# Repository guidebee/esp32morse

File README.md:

# Morse Code LoRa Walkie-Talkie

A battery-powered Morse code walkie-talkie built on the **TTGO LoRa32 v1** (ESP32). Type messages in Morse code using a physical key, transmit over LoRa radio, and receive messages on an OLED display — with multi-device support, AES encryption, and configurable channels.

[Watch Demo on YouTube](https://www.youtube.com/watch?v=TG7tIteto1E)

---

## Hardware

- **Board**: TTGO LoRa32 v1 (ESP32 + SX127x LoRa + SSD1306 OLED)
- **Framework**: PlatformIO / Arduino (C++)
- **Pins**:
  - `GPIO 35` — Battery level ADC
  - `GPIO 33` — Power switch
  - `GPIO 12` — Receiver LED
  - `GPIO 13` — Bluetooth LED

---

## Features

- **Morse code input** via physical key — short press = dit (`.`), long press = dah (`-`)
- **LoRa radio** for long-range communication (up to several kilometers)
- **OLED display** split into: scrolling top screen (received messages), bottom screen (composing), top bar (uptime/title), status bar (device/signal info + battery indicator)
- **Device discovery** — auto-tracks nearby nodes by chip ID and assigns short indexes
- **AES encryption** for secure message transmission
- **Multi-channel support** — configurable channel ID and LoRa sync word
- **Buzzer feedback** — audible dit/dah tones, message sent/received sounds, error beeps
- **BLE toggle** — optional Bluetooth support
- **Battery level indicator** in the status bar corner
- **Deep sleep support** (optional, disabled by default)

---

## Controls

| Button | Action |
|--------|--------|
| **Main** (short press) | Dit (`.`) |
| **Main** (long press) | Dah (`-`) |
| **Left** | Backspace (delete last character) |
| **Right** | Insert space |
| **OK** | Send message (if composing), or enter Options menu (press 3× when idle) |

Max message length is 36 characters — long messages are auto-sent when the limit is reached.

---

## Options Menu

Press **OK** three times while idle to enter the settings menu. Navigate with Left/Right, confirm with OK.

| Option | Description |
|--------|-------------|
| Device Name | Set a display name for this node |
| Play Sound | Toggle buzzer feedback on/off |
| Bluetooth | Enable/disable BLE |
| Channel Id | Set the channel number (numeric) |
| Sync Word | Set the LoRa sync word (0x00–0xFF) |
| Input Speed | Normal (150 ms threshold) or Fast (100 ms) |
| Exit | Return to main screen |

Settings are persisted to flash via the `Preferences` library.

---

## Build & Flash

### Requirements

- [PlatformIO](https://platformio.org/) (VS Code extension or CLI)

### Libraries (auto-installed via `platformio.ini`)

- `adafruit/Adafruit BusIO`
- `thijse/ArduinoLog`
- `arduinogetstarted/ezButton`
- `sandeepmistry/LoRa`
- `adafruit/Adafruit GFX Library`
- `adafruit/Adafruit SSD1306`

### Flash

Select the environment matching your OS:

```bash
# macOS
pio run -e ttgo-lora32-v1-mac -t upload

# Windows (default COM3)
pio run -e ttgo-lora32-v1-windows -t upload

# Linux
pio run -e ttgo-lora32-v1-unix -t upload
```

Adjust the `upload_port` in `platformio.ini` if your serial port differs.

---

## Message Protocol

Each LoRa packet includes the sender's chip ID and a message type:

| Type | Description |
|------|-------------|
| `HELLO` | Broadcast on startup; announces device name and enables discovery |
| `TEXT` | A Morse-decoded text message |
| `TEXT_ACK` | Acknowledgment of a received text message |

Received messages are displayed as `<index>:<device_name> <text>` in the top screen.

---

## Photos

| | |
|---|---|
|  |  |
|  |  |

---

## License

MIT

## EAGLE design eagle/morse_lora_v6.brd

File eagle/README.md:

# ESP32 Morse LoRa - PCB Design (Eagle)

PCB design for the LoRa Morse code walkie-talkie, designed in Autodesk EAGLE 9.6.2.

## Files

| File | Description |
|------|-------------|
| `morse_lora_v6.sch` | Latest schematic |
| `morse_lora_v6.brd` | Latest board layout |
| `morse_lora_v1–v5.*` | Prior revision history |

## Board Specs

- **Size**: ~55mm × 83mm (2.2" × 3.3")
- **Layers**: 2 (Top + Bottom)
- **Components**: 29 (through-hole / PTH)
- **Software**: EAGLE 9.6.2

## Bill of Materials (v6)

| Ref | Qty | Value | Description |
|-----|-----|-------|-------------|
| ESP32LORA | 1 | — | TTGO WiFi-LoRa-32 v1 module |
| C1–C4 | 4 | 0.1µF 50V | Decoupling capacitors |
| R1–R6 | 6 | 10kΩ 1/4W | Button pull-up/pull-down resistors |
| R7–R9 | 3 | 330Ω 1/10W | LED current limiting resistors |
| D-REC | 1 | Red 5mm LED | Receive indicator |
| D-BUT | 1 | Red 5mm LED | Button press feedback |
| D-BLU | 1 | Blue 5mm LED | Radio/BT status |
| RIGHT, LEFT, OK | 3 | 6mm switch | Navigation buttons (momentary PTH) |
| MAIN | 1 | 12mm switch | Main/power button (momentary PTH) |
| SLEEP | 1 | EG1218 | Sleep mode toggle switch |
| BUZZER | 1 | — | PTH electromechanical buzzer |

## Viewing the Files

Since EAGLE `.brd`/`.sch` files are XML-based, you can view them with:

- **[Autodesk EAGLE](https://www.autodesk.com/products/eagle/)** (free tier available) — full editing
- **[KiCad](https://www.kicad.org/)** with the EAGLE import plugin — open source
- **[EasyEDA](https://easyeda.com/)** — browser-based, supports EAGLE import
- **[Gerber viewers](https://www.pcbway.com/project/OnlineGerberViewer.html)** — after exporting Gerbers from EAGLE

## Design Revision History

| Version | Notes |
|---------|-------|
| v1 | Initial design — PTH switches, 5mm LEDs, discrete passives |
| v2 | Minor iteration on v1 |
| v3 | SMD redesign (0603 resistors, 1206 LEDs, SMD buzzer) — later reverted |
| v4 | Reverted to PTH; added SLEEP switch |
| v5 | Minor iteration on v4 |
| v6 | Added 330Ω LED current-limiting resistors (R7–R9); upgraded MAIN to 12mm switch |

The v3 SMD attempt was reverted in v4, settling on a PTH-first approach for easier hand-assembly and mechanical reliability of the buttons/switches.

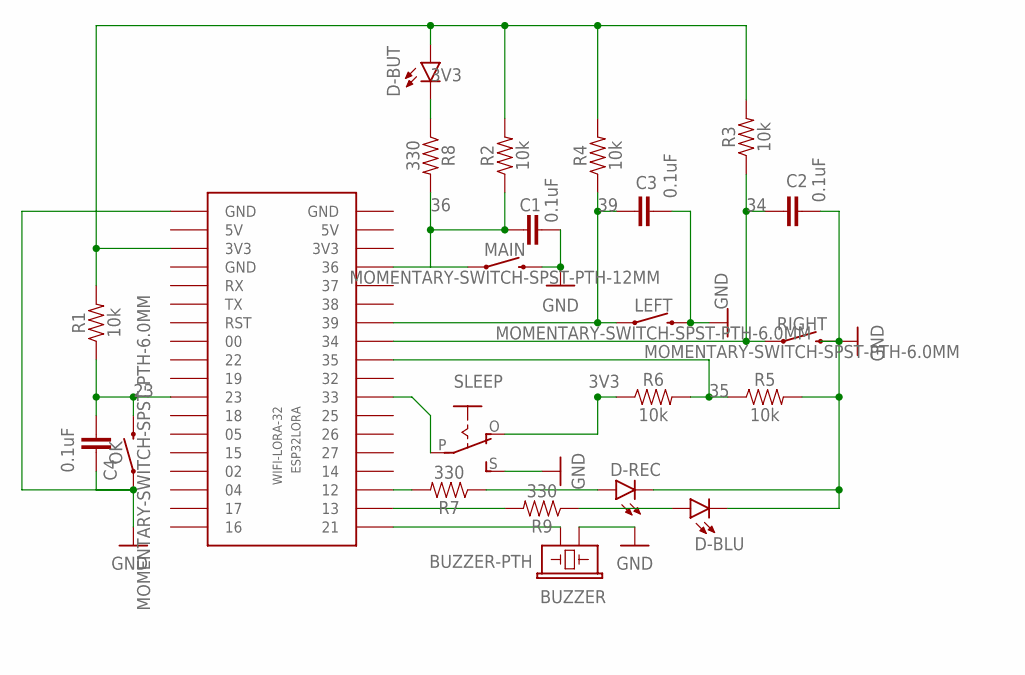
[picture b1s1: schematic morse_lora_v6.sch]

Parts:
BUZZER: BUZZER-PTH; BUZZER-12MM
C1, C2, C3, C4: 0.1uF; CAP-PTH-SMALL-KIT
D-BLU: LED5MM; LED_5MM
D-BUT: LED5MM; LED_5MM
D-REC: LED5MM; LED_5MM
ESP32LORA: WIFI-LORA-32; 2.54MM_2X18
LEFT: MOMENTARY-SWITCH-SPST-PTH-6.0MM; TACTILE_SWITCH_PTH_6.0MM
MAIN: MOMENTARY-SWITCH-SPST-PTH-12MM; TACTILE_SWITCH_PTH_12MM
OK: MOMENTARY-SWITCH-SPST-PTH-6.0MM; TACTILE_SWITCH_PTH_6.0MM
R1, R2, R3, R4, R5, R6: 10k; AXIAL-0.3-KIT
R7, R8, R9: 330; AXIAL-0.3
RIGHT: MOMENTARY-SWITCH-SPST-PTH-6.0MM; TACTILE_SWITCH_PTH_6.0MM
SLEEP: EG1218S; EG1218

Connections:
3V3: D-BUT.A, ESP32LORA.P$3 (3V3), R1.P$2 (2), R2.P$2 (2), R3.P$2 (2), R4.P$2 (2), R6.P$1 (1), SLEEP.O
23: C4.2, ESP32LORA.P$11 (23), OK.3 (2), R1.P$1 (1)
34: C2.2, ESP32LORA.P$29 (34), R3.P$1 (1), RIGHT.1
35: ESP32LORA.P$28 (35), R5.P$1 (1), R6.P$2 (2)
36: C1.2, ESP32LORA.P$33 (36), MAIN.1, R2.P$1 (1), R8.P$2 (2)
39: C3.1, ESP32LORA.P$30 (39), LEFT.1, R4.P$1 (1)
GND: BUZZER.- (2), C1.1, C2.1, C3.2, C4.1, D-BLU.K (C), D-REC.K (C), ESP32LORA.P$1 (GND), LEFT.3 (2), MAIN.3 (2), OK.1, R5.P$2 (2), RIGHT.3 (2), SLEEP.S
unnamed: ESP32LORA.P$21 (12), R7.P$2 (2)
unnamed: D-BUT.K (C), R8.P$1 (1)
unnamed: D-BLU.A, R9.P$1 (1)
unnamed: BUZZER.+ (1), ESP32LORA.P$19 (21)
unnamed: D-REC.A, R7.P$1 (1)
unnamed: ESP32LORA.P$20 (13), R9.P$2 (2)
unnamed: ESP32LORA.P$26 (33), SLEEP.P

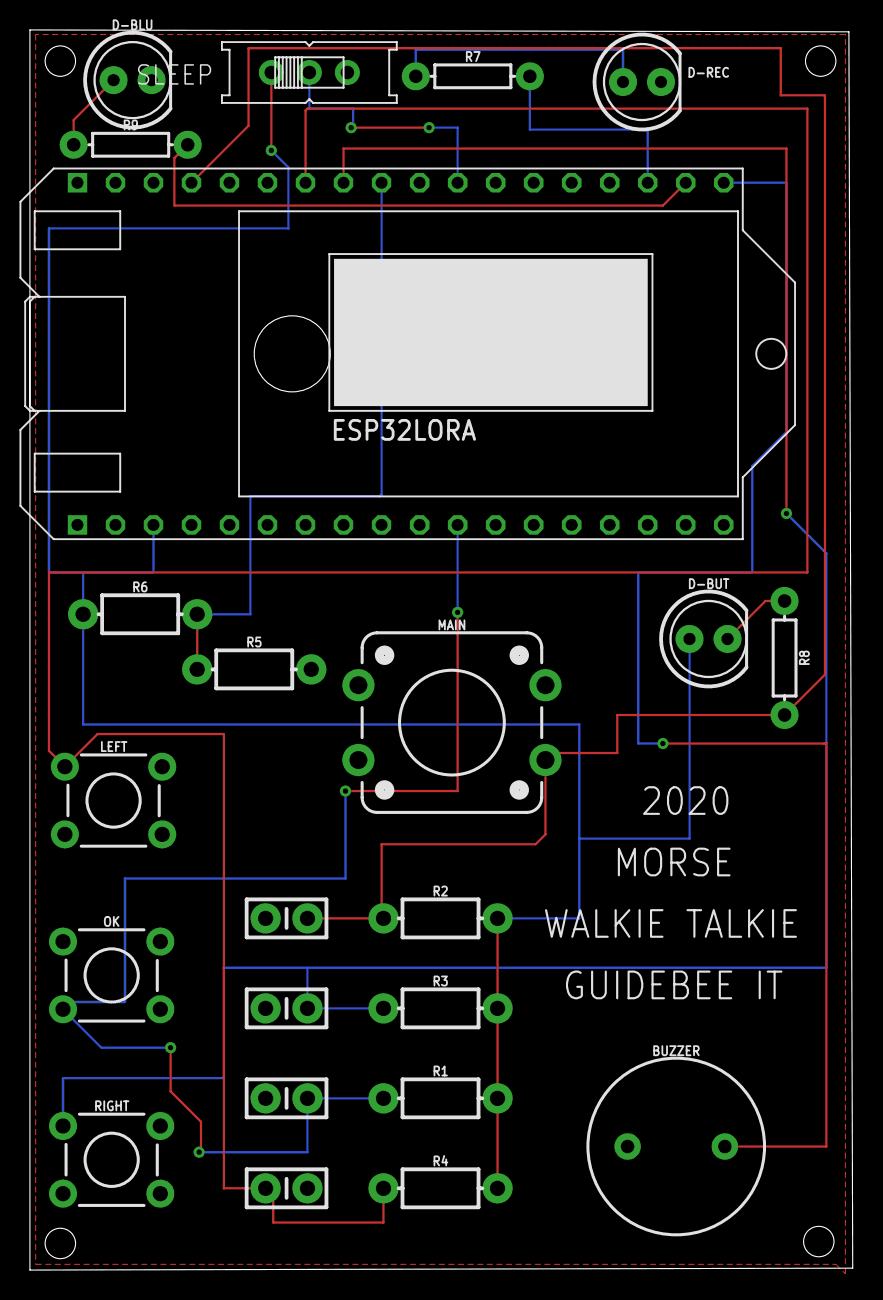
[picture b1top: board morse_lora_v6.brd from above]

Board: 2 copper layers, 55.0 x 82.9 mm, 23 parts (0 on the bottom side), 14 nets.

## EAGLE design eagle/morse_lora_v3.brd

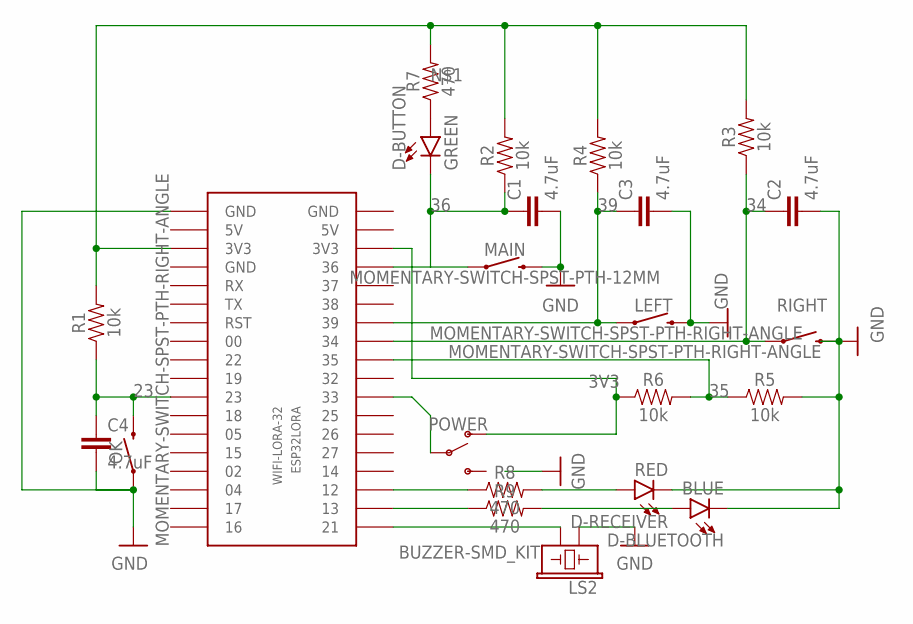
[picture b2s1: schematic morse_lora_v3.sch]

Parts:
C1, C2, C3, C4: 4.7uF; 0603
D-BLUETOOTH: BLUE; LED-1206
D-BUTTON: GREEN; LED-1206
D-RECEIVER: RED; LED-1206
ESP32LORA: WIFI-LORA-32; 2.54MM_2X18
LEFT: MOMENTARY-SWITCH-SPST-PTH-RIGHT-ANGLE; TACTILE_SWITCH_PTH_RIGHT_ANGLE
LS2: BUZZER-SMD_KIT; BUZZER-CCV-KIT
MAIN: MOMENTARY-SWITCH-SPST-PTH-12MM; TACTILE_SWITCH_PTH_12MM
OK: MOMENTARY-SWITCH-SPST-PTH-RIGHT-ANGLE; TACTILE_SWITCH_PTH_RIGHT_ANGLE
POWER: SWITCH-SPDT-SMD-RIGHT-ANGLE; SWITCH_SPST_SMD_A
R1, R2, R3, R4, R5, R6: 10k; 0603
R7, R8, R9: 470; 0603
RIGHT: MOMENTARY-SWITCH-SPST-PTH-RIGHT-ANGLE; TACTILE_SWITCH_PTH_RIGHT_ANGLE

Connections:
3V3: ESP32LORA.P$3 (3V3), ESP32LORA.P$34 (3V3), POWER.1 (O), R1.2, R2.2, R3.2, R4.2, R6.1, R7.2
23: C4.1, ESP32LORA.P$11 (23), OK.2, R1.1
34: C2.1, ESP32LORA.P$29 (34), R3.1, RIGHT.1
35: ESP32LORA.P$28 (35), R5.1, R6.2
36: C1.1, D-BUTTON.C, ESP32LORA.P$33 (36), MAIN.1, R2.1
39: C3.1, ESP32LORA.P$30 (39), LEFT.1, R4.1
GND: C1.2, C2.2, C3.2, C4.2, D-BLUETOOTH.C, D-RECEIVER.C, ESP32LORA.P$1 (GND), LEFT.2, LS2.+ (1), MAIN.3 (2), OK.1, R5.2, RIGHT.2
unnamed: D-BUTTON.A, R7.1
unnamed: D-RECEIVER.A, R8.2
unnamed: ESP32LORA.P$20 (13), R9.1
unnamed: ESP32LORA.P$19 (21), LS2.- (2)
unnamed: ESP32LORA.P$21 (12), R8.1
unnamed: D-BLUETOOTH.A, R9.2
unnamed: ESP32LORA.P$26 (33), POWER.2

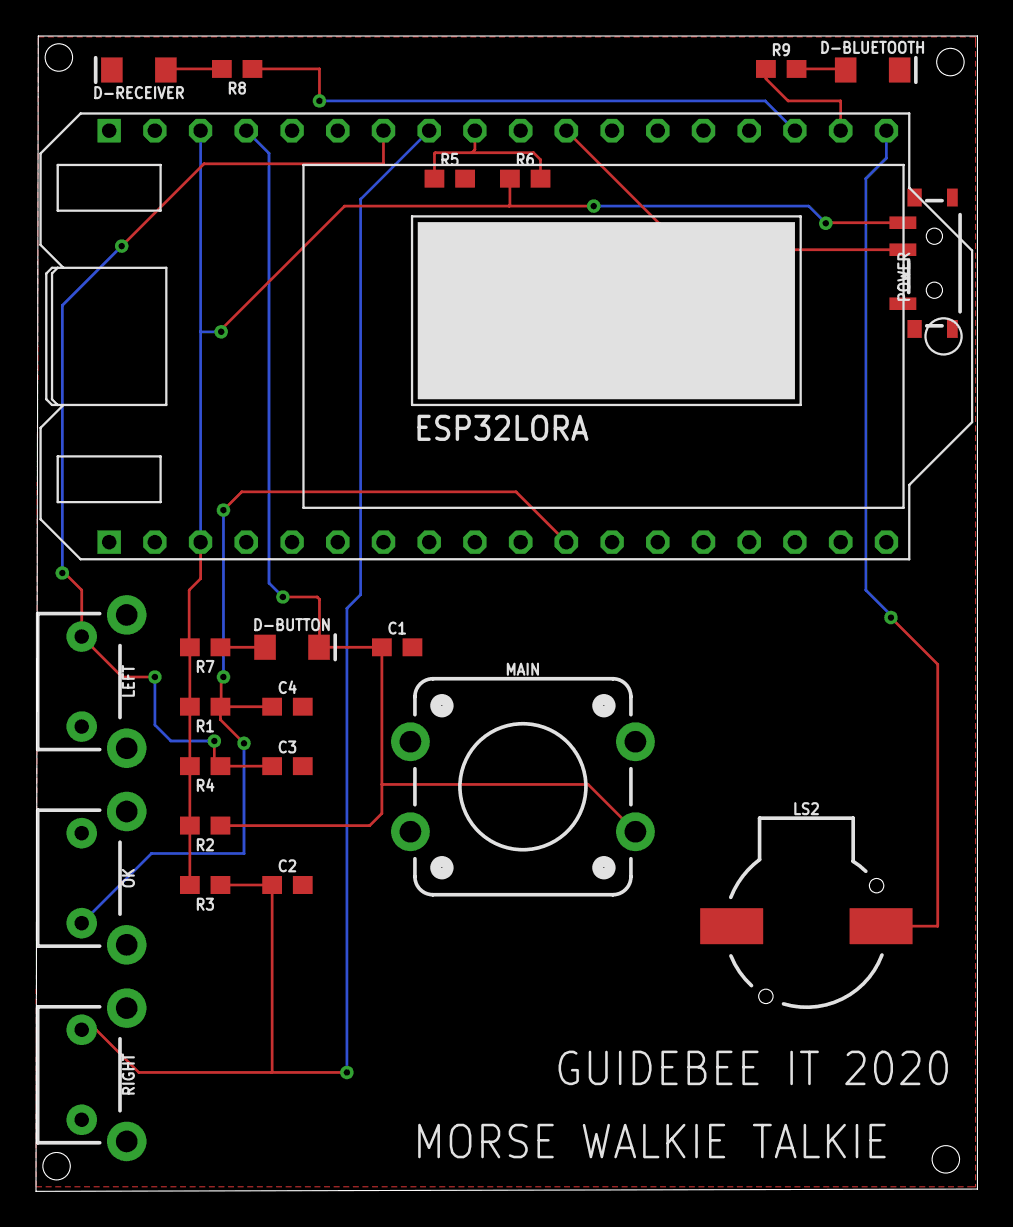
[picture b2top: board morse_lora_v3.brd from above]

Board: 2 copper layers, 52.3 x 64.2 mm, 23 parts (0 on the bottom side), 14 nets.

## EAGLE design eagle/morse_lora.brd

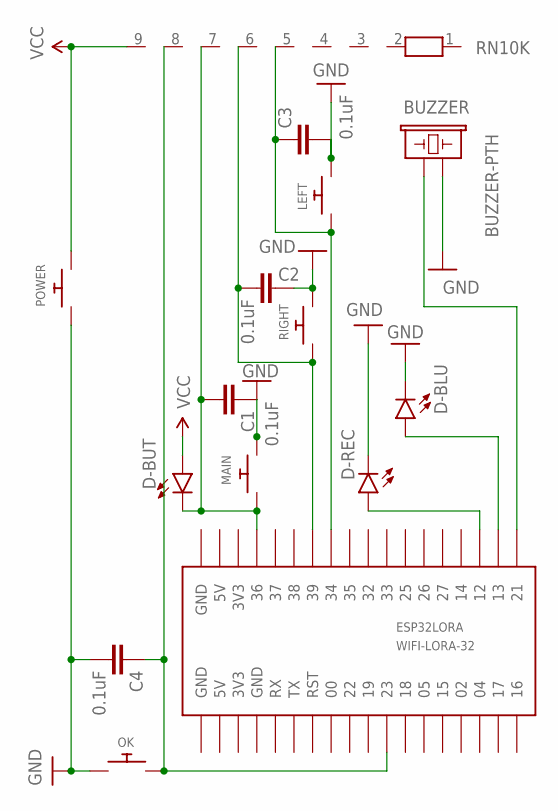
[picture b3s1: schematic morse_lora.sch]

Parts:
BUZZER: BUZZER-PTH; BUZZER-12MM
C1, C2, C3, C4: 0.1uF; CAP-PTH-SMALL-KIT
D-BLU: LED5MM; LED_5MM
D-BUT: LED5MM; LED_5MM
D-REC: LED5MM; LED_5MM
ESP32LORA: WIFI-LORA-32; 2.54MM_2X18
LEFT: SWITCH_PUSHBUTTONEVQ-PE; TACT_PANA-EVQ
MAIN: SWITCH_PUSHBUTTONEVQ-PE; TACT_PANA-EVQ
OK: SWITCH_PUSHBUTTONEVQ-PE; TACT_PANA-EVQ
POWER: SWITCH_PUSHBUTTONEVQ-PE; TACT_PANA-EVQ
RIGHT: SWITCH_PUSHBUTTONEVQ-PE; TACT_PANA-EVQ
RN10K: RN08; RN-9

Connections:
GND: BUZZER.- (2), C1.1, C2.1, C3.2, C4.2, D-BLU.K (C), D-REC.K (C), LEFT.P$2, MAIN.P$2, OK.P$1, POWER.P$1, RIGHT.P$2
unnamed: C1.2, D-BUT.K (C), ESP32LORA.P$33 (36), MAIN.P$1, RN10K.7
unnamed: C2.2, ESP32LORA.P$30 (39), RIGHT.P$1, RN10K.6
unnamed: C3.1, ESP32LORA.P$29 (34), LEFT.P$1, RN10K.5
unnamed: BUZZER.+ (1), ESP32LORA.P$19 (21)
unnamed: D-REC.A, ESP32LORA.P$21 (12)
unnamed: D-BLU.A, ESP32LORA.P$20 (13)
unnamed: C4.1, ESP32LORA.P$11 (23), OK.P$2, RN10K.8
VCC: D-BUT.A, POWER.P$2, RN10K.9

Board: 2 copper layers, 15 parts (0 on the bottom side), 9 nets, no tracks yet.

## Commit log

2020-08-23 start the project esp32 morse code walkie talkie
2020-09-18 refactor oled display
2020-09-18 add sound tone
2020-09-19 add lora radio
2020-09-19 refactor
2020-09-19 draft simple screen
2020-09-19 screen
2020-09-19 add backspace
2020-09-19 handle return
2020-09-24 add missing libs
2020-09-26 remove delay and add led and audio class
2020-09-27 add bluetooth led
2020-09-27 add keypad
2020-09-27 add morse walkie talkie
2020-09-27 fix display in input area
2020-09-27 add error sound
2020-09-27 add mute sound option
2020-09-27 dynamic screen
2020-09-28 refactor lora radio
2020-09-28 encode decode
2020-09-28 heart beat message
2020-09-28 encrption/decryption
2020-09-28 encryption/decryption
2020-09-28 add user name
2020-09-28 preference
2020-09-28 minor changes
2020-09-29 change pins
2020-09-29 add menu option
2020-09-29 add channel id checking
2020-09-29 add message ack
2020-09-29 add payload length check
2020-09-30 remove offset for chat area
2020-09-30 add default device name
2020-10-01 only decryption message itself
2020-10-01 add encryption flag in the message
2020-10-01 default morse user
2020-10-01 draft menu option
2020-10-01 refactor ,add base view
2020-10-01 draft option menu
2020-10-02 display options
2020-10-02 save device name, sync word and channel id
2020-10-02 options
2020-10-03 add schmetic
2020-10-04 add power switch
2020-10-04 add power icon
2020-10-04 draw battery level
2020-10-04 rotate schematic
2020-10-05 draft layout
2020-10-06 change chip to 16 bytes
2020-10-06 revert back to broken change (no message received)
2020-10-06 add back device checking
2020-10-06 fix backspace
2020-10-17 add pcb v2
2020-10-17 update pcb v1
2020-10-23 update pcb v2
2020-10-23 add support sleep
2020-10-24 fix typo
2020-10-29 board v3 and v4
2020-10-31 board v5
2020-10-31 #6 random hello message
2020-10-31 #6 use queue to send messages
2020-10-31 turn off sound in option mode
2020-10-31 draw battery level more often
2020-11-03 optimize start up
2020-11-05 rough battery level
2020-11-05 display up time
2020-11-05 display uptime
2020-11-08 v6 board
2020-11-11 option to swap led
2020-11-15 add windows configuration
2025-07-12 add some images

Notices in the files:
parts and their libraries:
SparkFun-Electromechanical: Licensing: Creative Commons ShareAlike 4.0 International - https://creativecommons.org/licenses/by-sa/4.0
